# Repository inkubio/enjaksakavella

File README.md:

# Enjaksakavella

This is a project to control an electric wheelchair with custom controllers.

Project parts:
- Electronics connecting to wheelchair
- BLE-enabled Arduino driving the electronics
- Computer with software which handles:
  - BLE connection to Arduino
  - Connection to controllers
  - Visualizing controller working principles
  - Visualizing commands sent to wheelchair
- Custom controller(s)
  - Cap with eye-tracking camera

## Requirements

### Python Packages
- General (Qt)
  - PySide2
- Bluetooth on Linux
  - pydbus
  - python3-gi (from distribution repositories)
  - vext
  - vext<span></span>.gi (for python3-gi)
- For Eyetracker controller
  - OpenCV2
  - numpy

### Arduino Libraries:
- ArduinoBLE

## Documentation

More documentation can be found in /doc folder

## Quick Start Guide
Using a laptop with linux and BLE-capable bluetooth

### Install software on computer

1. Clone the git repository

        git clone https://github.com/inkubio/enjaksakavella.git

2. Create a new virtual environment for the project and activate it

        cd enjaksakavella
        python3 -m venv .venv
        source .venv/bin/activate

    When running the program, remember activate this virtual environment first by running the activate script.

3. Install required software, with python packages in the virtual environment

    For Qt:

        pip3 install pyside2

    For DBus:

        pip3 install pydbus

    For DBus error handling use system's GObject Inspector since the packages can't be found on pip. First, ensure that you have python3-gi installed:

        sudo apt install python3-gi

    For compiling python modules:

        sudo apt install python3-dev

    For Qt wayland support:
        sudo apt install qtwayland5

    Then install vext package to use python3-gi

        pip3 install vext --no-binary :all:
        pip3 install vext.gi --no-binary :all:

    For Eyetracker: (opencv-python also installs numpy)

        pip3 install opencv-python

    For acceleration glasses:
        pip3 install phidget22

        Additionally, install the libphidget22 library to /usr/lib, for example by following these compile instructions: https://www.phidgets.com/docs/OS_-_Linux#Source%20Install . Remember to also add the udev-rule!

    Check that you get something like this with `pip3 list` and the setup should be done.

        (.venv) tuomas@blini:~/Ohjelmointi/enjaksakavella/src$ pip3 list
        Package          Version 
        ---------------- --------
        numpy            1.22.3
        opencv-python    4.5.5.64
        Phidget22        1.10.20220211
        pip              20.3.4
        pkg-resources    0.0.0
        pydbus           0.6.0
        PySide2          5.15.2.1
        ruamel.yaml      0.17.21
        ruamel.yaml.clib 0.2.6
        setuptools       44.1.1
        shiboken2        5.15.2.1
        vext             0.7.6
        vext.gi          0.7.4

### Control the wheelchair
1. Connect the electronics to RNET OMNI's port 1
2. Turn on the wheelchair from RNET OMNI
3. Set control program to 3 from RNET OMNI
4. Run `main.py` in `src` folder
  - You may need to specify using Wayland on newer OS versions: `python main.py -platform wayland`
5. Select Bluetooth wheelchair and click connect
6. Select your favourite controller from the GUI
7. Enable desired movement(s) from the GUI
8. Move around without the need to use your legs

You should see this after step 3:

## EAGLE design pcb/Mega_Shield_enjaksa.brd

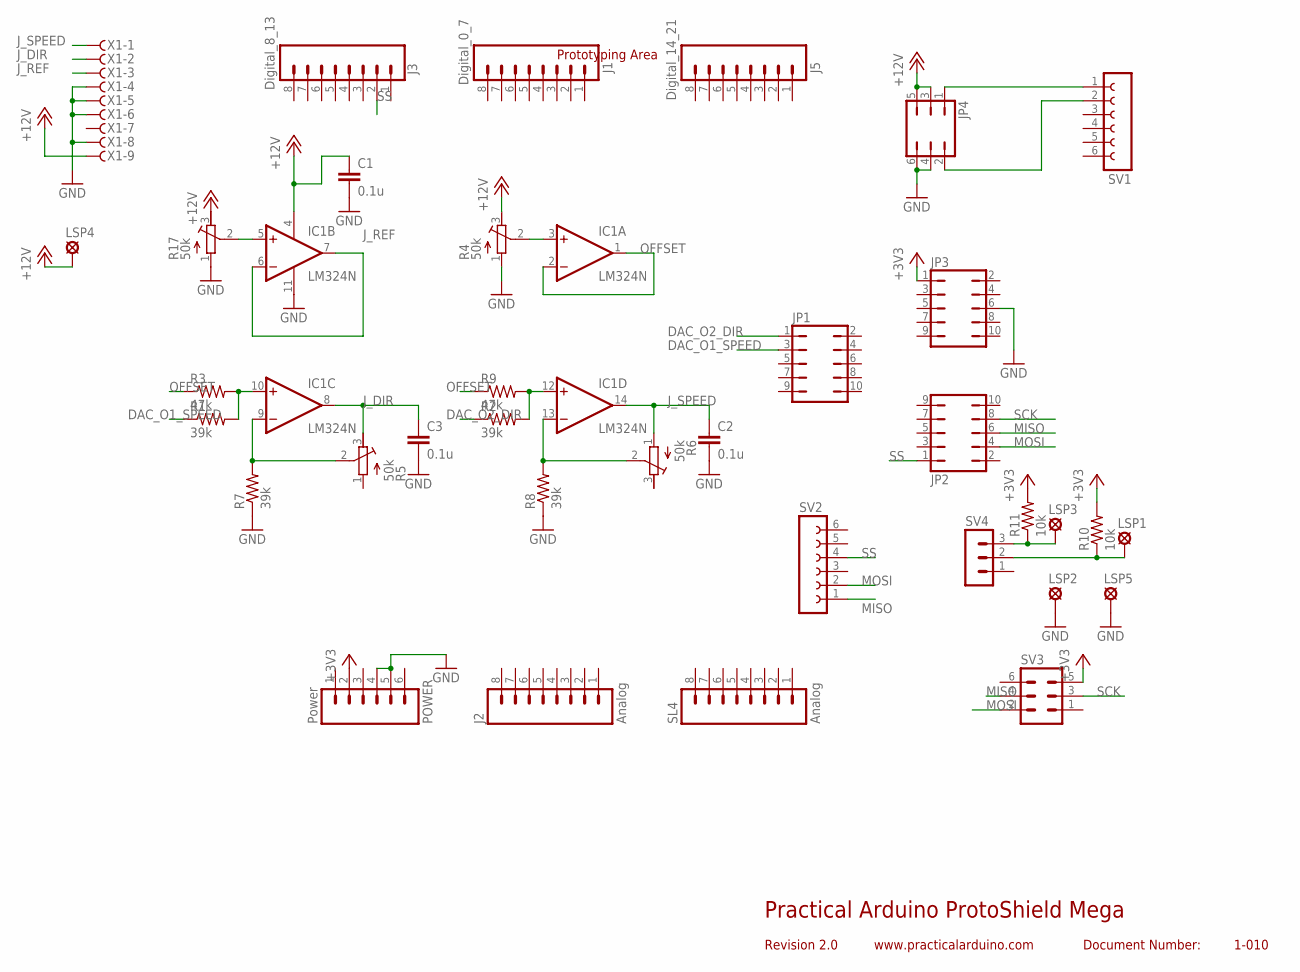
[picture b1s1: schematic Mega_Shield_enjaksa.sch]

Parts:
C1, C3: 0.1u; C025-024X044
C2: 0.1u; C050-025X075
IC1: LM324N; DIL14
J1: Digital_0_7; 1X08
J2: Analog; 1X08
J3: Digital_8_13; 1X08
J5: Digital_14_21; 1X08
JP1, JP2, JP3: JP5Q
JP4: JP3Q
LSP1, LSP2, LSP3, LSP4, LSP5: SE13
POWER: Power; 1X06
R1, R2, R7: 39k; 0204/7
R3, R9: 47k; 0204/7
R4, R5, R6, R17: 50k; RTRIM64W
R8: 39k; 0204V
R10, R11: 10k; 0204V
SL4: Analog; 1X08
SV1, SV2: FE06-1; FE06
SV3: MA03-2
SV4: MA03-1
X1: F09HS; F09H

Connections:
+3V3: JP3.1, POWER.2, R10.2, R11.2, SV3.5
+12V: C1.1, IC1.4 (V+), JP4.3, JP4.5, LSP4.MP, R4.3 (E), R17.3 (E), X1.9
DAC_O1_SPEED: JP1.3, R1.1
DAC_O2_DIR: JP1.1, R2.1
GND: C1.2, C2.2, C3.2, IC1.11 (V-), JP3.6, JP4.4, JP4.6, LSP2.MP, LSP5.MP, POWER.4, POWER.5, R4.1 (A), R7.1, R8.1, R17.1 (A), X1.4, X1.5, X1.6, X1.8
J_DIR: C3.1, IC1.8 (OUT), R5.3 (E), X1.2
J_REF: IC1.6 (-IN), IC1.7 (OUT), X1.3
J_SPEED: C2.1, IC1.14 (OUT), R6.1 (A), X1.1
MISO: JP2.6, SV2.1, SV3.4
MOSI: JP2.4, SV2.2, SV3.2
unnamed: JP4.2, SV1.2
unnamed: IC1.5 (+IN), R17.2 (S)
unnamed: IC1.3 (+IN), R4.2 (S)
unnamed: JP4.1, SV1.1
unnamed: LSP3.MP, R11.1, SV4.3
unnamed: LSP1.MP, R10.1, SV4.2
unnamed: IC1.13 (-IN), R6.2 (S), R8.2
unnamed: IC1.12 (+IN), R2.2, R9.2
unnamed: IC1.9 (-IN), R5.2 (S), R7.2
unnamed: IC1.10 (+IN), R1.2, R3.2
OFFSET: IC1.1 (OUT), IC1.2 (-IN), R3.1, R9.1
SCK: JP2.8, SV3.3
SS: J3.2, JP2.1, SV2.4

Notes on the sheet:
Prototyping Area
Practical Arduino ProtoShield Mega
Revision 2.0
www.practicalarduino.com
Document Number:
1-010

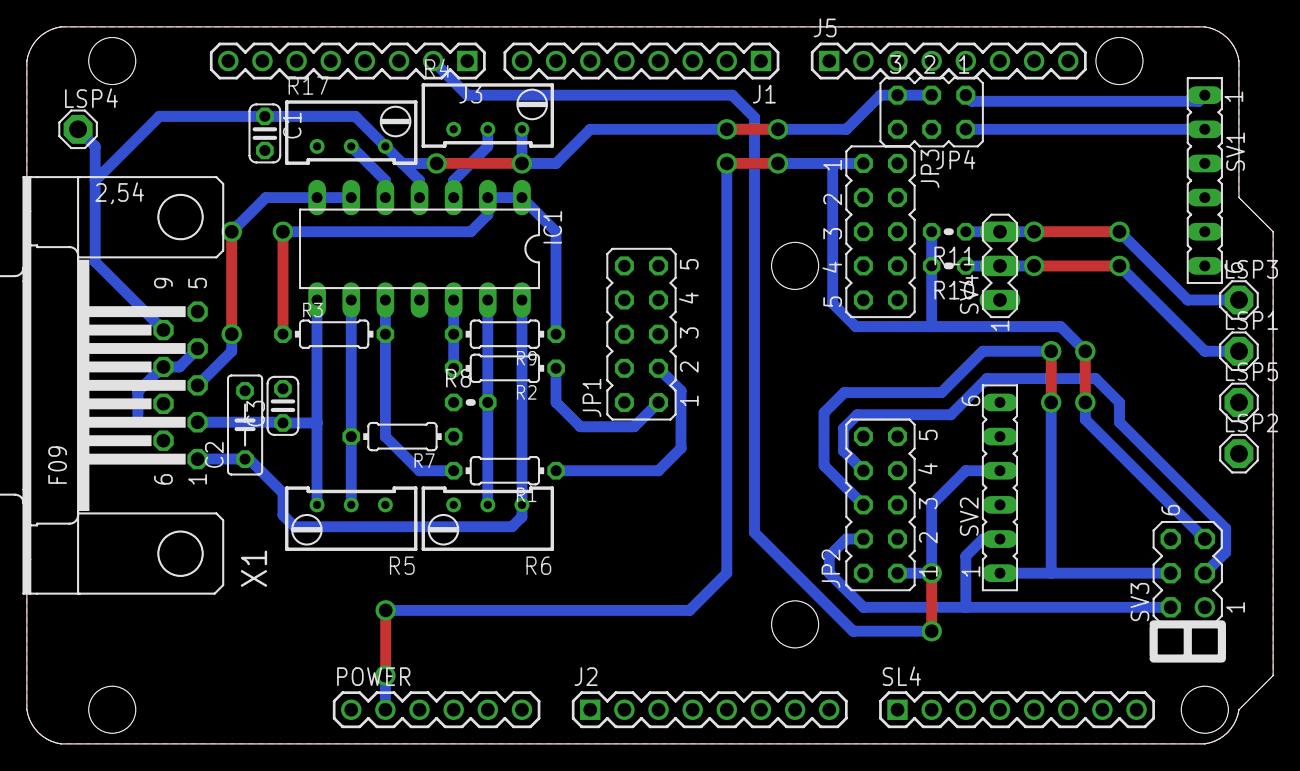
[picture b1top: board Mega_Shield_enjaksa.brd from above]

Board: 2 copper layers, 92.7 x 53.3 mm, 36 parts (0 on the bottom side), 23 nets.

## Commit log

2020-02-18 Added rest of the system parts
2020-02-18 Added initial PCB schematics
2020-02-18 Added TODO list
2020-02-19 Moved some TODOs from documentation
2020-02-19 Updated documentation to reflect current system
2020-04-07 Use bluetooth with dbus
2020-04-08 Add installation instructions
2020-04-08 Update documentation
2020-04-08 Update TODO
2020-04-09 Add .gitignore
2020-04-09 Add indication that the software is attempting to connect
2020-04-09 Remove an "s" left behind
2020-04-10 Fix crash when quitting program
2020-04-11 Improve exception handling
2020-04-11 Add platform-specific BLE connection implementation
2020-04-21 Change EDA software (and file format) from EAGLE to KiCad
2022-03-16 Update instructions for newer OS versions
2022-03-16 Prevent infinite loop if closing app while connecting with BLE
2022-03-16 Release keys automatically
2022-03-21 Improve responsiveness
2022-03-21 Make bluetooth communication non-blocking
2022-03-25 Update pcb files to new KiCad version
2022-03-25 Add accelerometer glasses controller
2022-03-25 Add Phidget22 to pip list example
2022-03-25 Add libphidget22.so to repo
2022-03-25 Fix instructions for installing libphidget22
2022-03-25 Add reminder for installing the udev rules
